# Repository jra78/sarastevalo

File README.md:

# sarastevalo
"Sarastevalo eagle" hekemistosta löytyy piirilevyä varten eagle tiedostot (useampia versioita)
"Sarastevalo arduino" hakemistosta löytyy koodi

in "Sarastevalo eagle"-folder is eagle files (multiple versions)
in "Sarastevalo arduino" folder is code

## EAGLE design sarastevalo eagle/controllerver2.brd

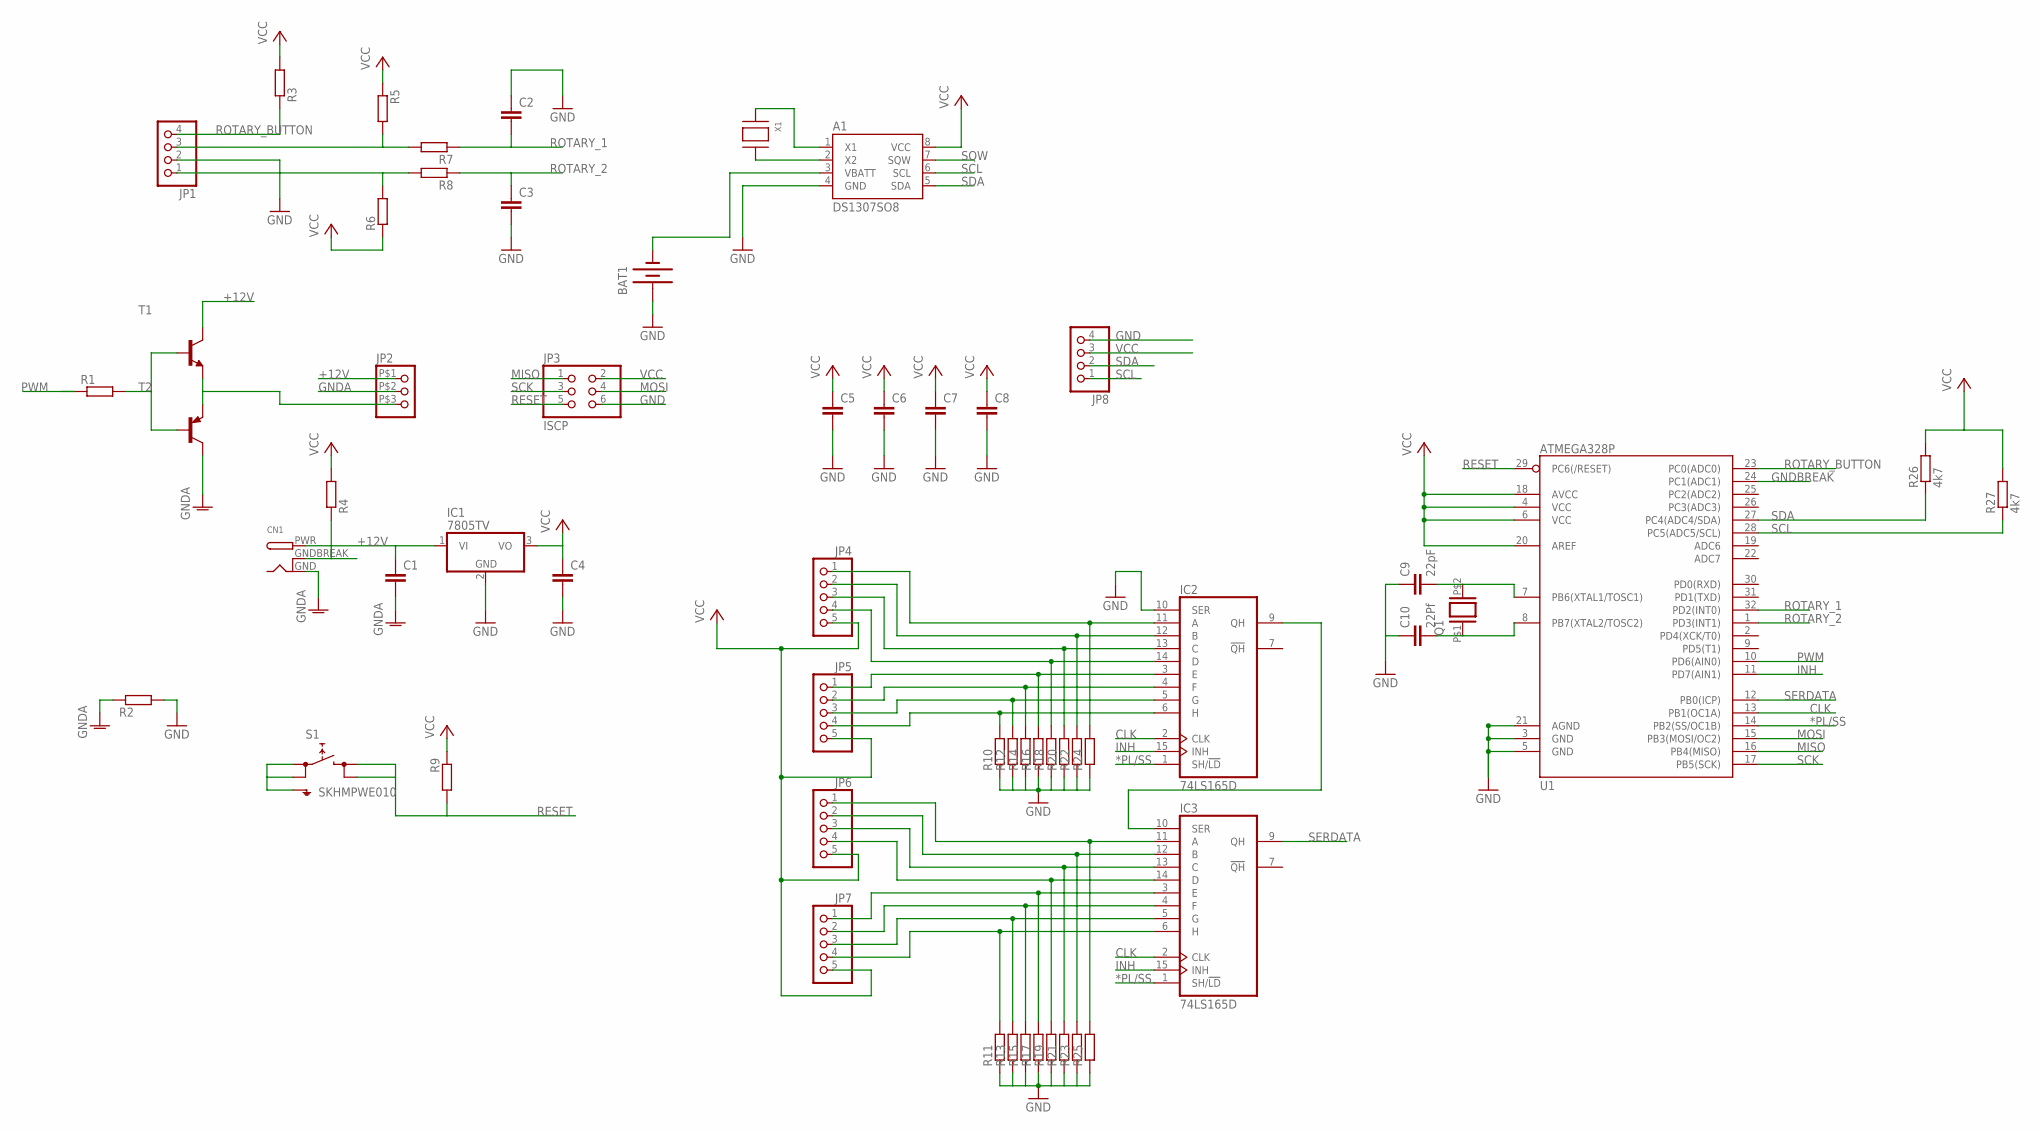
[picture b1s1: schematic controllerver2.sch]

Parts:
A1: DS1307SO8; SO08
BAT1: BATTERY20SMD; BATTCON_20MM
C1, C2, C3, C4, C5, C6, C7, C8: C-EUC0805; C0805
C9: 22pF; C0805
C10: 22Pf; C0805
CN1: DCBARRELPTH; DCJACK_2MM_PTH
IC1: 7805TV; TO220V
IC2, IC3: 74LS165D; SO16
JP1, JP8: PINHD-1X4; 1X04
JP2: PINHD-1X35.08; 1X03/5.08
JP3: ISCP; 2X03
JP4, JP5, JP6, JP7: PINHD-1X5; 1X05
Q1: XTAL; CSM-3X
R1, R2, R3, R4, R5, R6, R7, R8, R9, R10, R11, R12, R13, R14, R15, R16, R17, R18, R19, R20, R21, R22, R23, R24, R25: R-EU_R0805; R0805
R26, R27: 4k7; R0805
S1: SKHMPWE010; SKHMPXE010
T1: BC847-NPN-SOT23-BEC; SOT23-BEC
T2: BC807-16-PNP-SOT23-BEC; SOT23-BEC
U1: ATMEGA328P; TQFP32-08
X1: XTAL-3.2X1.5; XTAL3215

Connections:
*PL/SS: IC2.1 (SH/!LD), IC3.1 (SH/!LD), U1.14 (PB2(SS/OC1B))
+12V: C1.1, CN1.PWR, IC1.1 (VI), JP2.P$1 (1), T1.C
CLK: IC2.2 (CLK), IC3.2 (CLK), U1.13 (PB1(OC1A))
GND: A1.4 (GND), BAT1.1 (+), C2.1, C3.2, C4.2, C5.2, C6.2, C7.2, C8.2, C9.1, C10.1, IC1.2 (GND), IC2.8 (GND), IC2.10 (SER), IC3.8 (GND), JP1.2, JP3.6, JP8.4, R2.2, R10.1, R11.1, R12.1, R13.1, R14.1, R15.1, R16.1, R17.1, R18.1, R19.1, R20.1, R21.1, R22.1, R23.1, R24.1, R25.1, S1.1 (1.1), S1.2 (1.2), S1.5 (SH), U1.3 (GND), U1.5 (GND), U1.21 (AGND)
GNDA: C1.2, CN1.GND, JP2.P$2 (2), R2.1, T2.C
GNDBREAK: CN1.GNDBREAK, R4.1, U1.24 (PC1(ADC1))
INH: IC2.15 (INH), IC3.15 (INH), U1.11 (PD7(AIN1))
MISO: JP3.1, U1.16 (PB4(MISO))
MOSI: JP3.4, U1.15 (PB3(MOSI/OC2))
unnamed: IC2.11 (A), JP4.1, R24.2
unnamed: IC2.12 (B), JP4.2, R22.2
unnamed: IC2.13 (C), JP4.3, R20.2
unnamed: IC2.14 (D), JP4.4, R18.2
unnamed: IC2.3 (E), JP5.1, R16.2
unnamed: IC2.4 (F), JP5.2, R14.2
unnamed: IC2.5 (G), JP5.3, R12.2
unnamed: IC2.6 (H), JP5.4, R10.2
unnamed: IC3.11 (A), JP6.1, R25.2
unnamed: IC3.12 (B), JP6.2, R23.2
unnamed: IC3.13 (C), JP6.3, R21.2
unnamed: IC3.14 (D), JP6.4, R19.2
unnamed: IC3.3 (E), JP7.1, R17.2
unnamed: IC3.4 (F), JP7.2, R15.2
unnamed: IC3.5 (G), JP7.3, R13.2
unnamed: IC3.6 (H), JP7.4, R11.2
unnamed: JP1.3, R5.2, R7.2
unnamed: JP2.P$3 (3), T1.E, T2.E
unnamed: JP1.1, R6.2, R8.2
unnamed: IC2.9 (QH), IC3.10 (SER)
unnamed: A1.3 (VBATT), BAT1.2 (-)
unnamed: C9.2, Q1.P$2 (2), U1.7 (PB6(XTAL1/TOSC1))
unnamed: C10.2, Q1.P$1 (1), U1.8 (PB7(XTAL2/TOSC2))
unnamed: R1.2, T1.B, T2.B
unnamed: A1.2 (X2), X1.P$2
unnamed: A1.1 (X1), X1.P$1
PWM: R1.1, U1.10 (PD6(AIN0))
RESET: JP3.5, R9.2, S1.3 (2.1), S1.4 (2.2), U1.29 (PC6(/RESET))
ROTARY_1: C2.2, R7.1, U1.32 (PD2(INT0))
ROTARY_2: C3.1, R8.1, U1.1 (PD3(INT1))
ROTARY_BUTTON: JP1.4, R3.1, U1.23 (PC0(ADC0))
SCK: JP3.3, U1.17 (PB5(SCK))
SCL: A1.6 (SCL), JP8.1, R27.1, U1.28 (PC5(ADC5/SCL))
SDA: A1.5 (SDA), JP8.2, R26.1, U1.27 (PC4(ADC4/SDA))
SERDATA: IC3.9 (QH), U1.12 (PB0(ICP))
SQW: A1.7 (SQW)
VCC: A1.8 (VCC), C4.1, C5.1, C6.1, C7.1, C8.1, IC1.3 (VO), IC2.16 (VCC), IC3.16 (VCC), JP3.2, JP4.5, JP5.5, JP6.5, JP7.5, JP8.3, R3.2, R4.2, R5.1, R6.1, R9.1, R26.2, R27.2, U1.4 (VCC), U1.6 (VCC), U1.18 (AVCC), U1.20 (AREF)

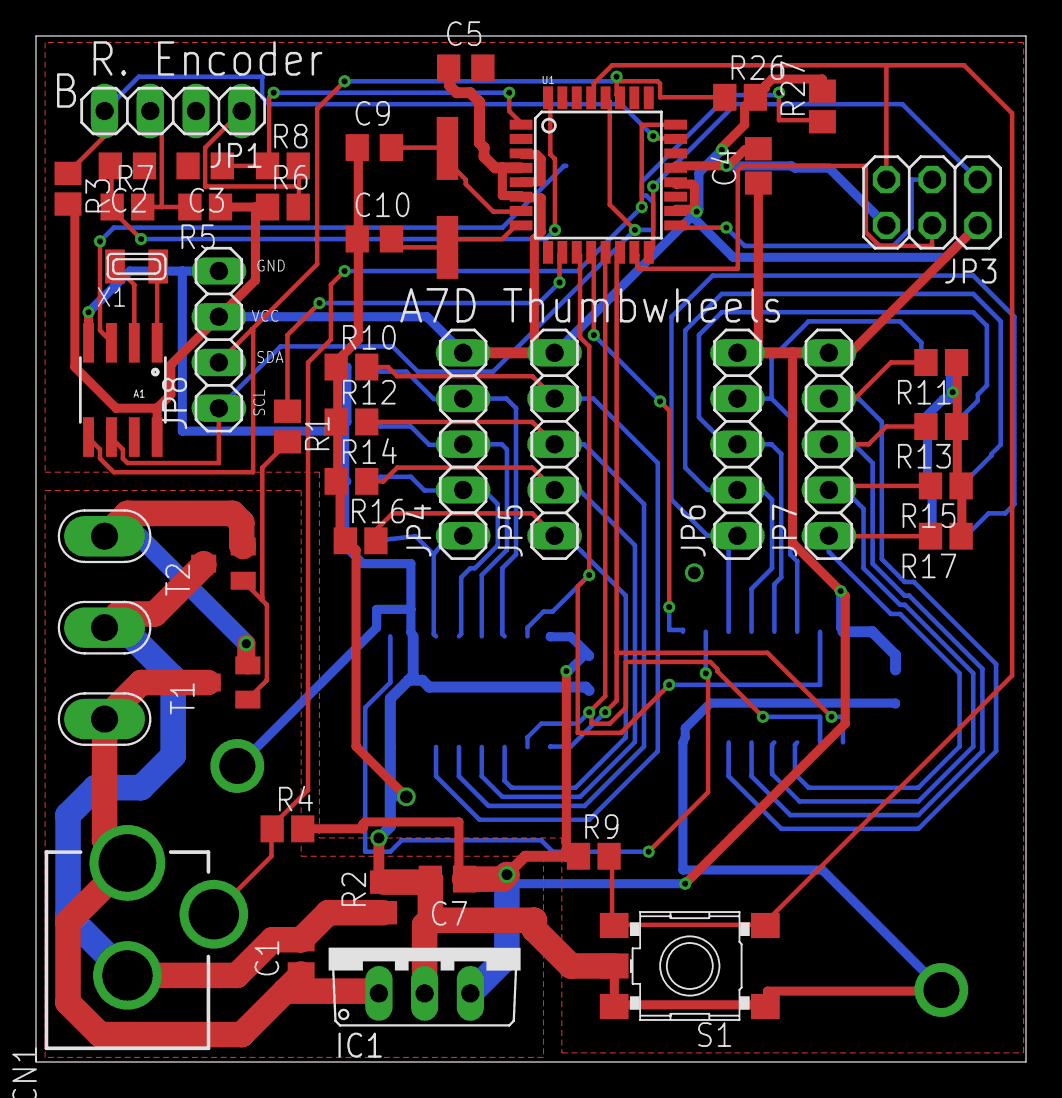
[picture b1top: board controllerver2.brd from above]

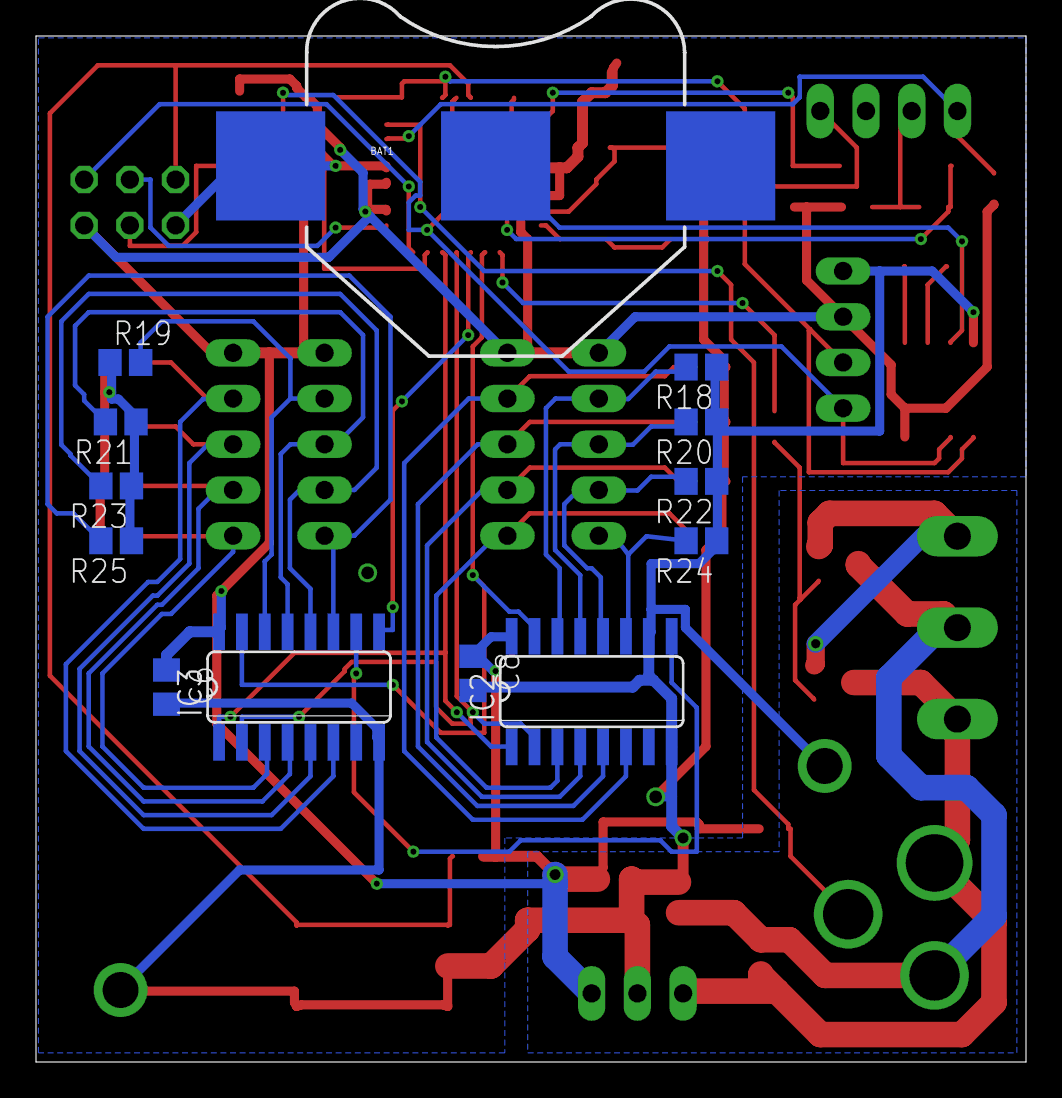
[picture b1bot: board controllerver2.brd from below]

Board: 2 copper layers, 55.0 x 57.0 mm, 57 parts (13 on the bottom side), 45 nets.

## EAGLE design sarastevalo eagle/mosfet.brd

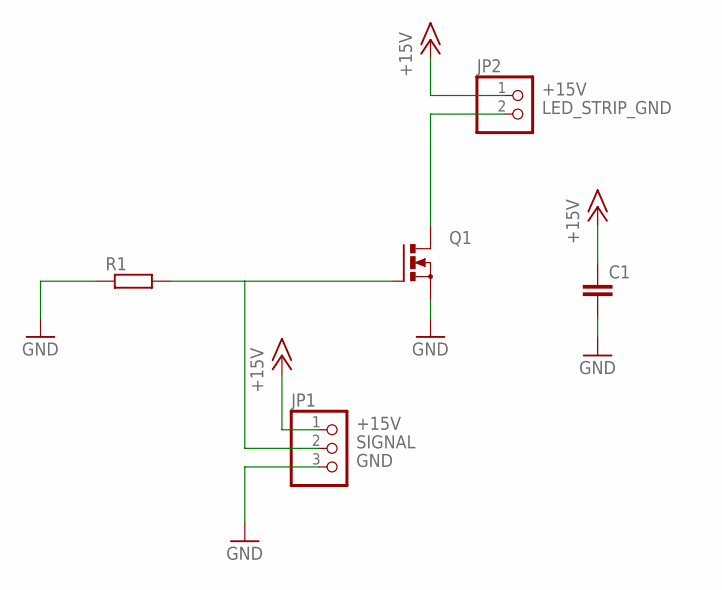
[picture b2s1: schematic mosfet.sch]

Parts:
C1: C-EU050-025X075; C050-025X075
JP1: PINHD-1X3; 1X03
JP2: PINHD-1X2; 1X02
Q1: PMOSFET_NTO220BV; TO220BV
R1: R-EU_M0805; M0805

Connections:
+15V: C1.1, JP1.1, JP2.1
GND: C1.2, JP1.3, Q1.S, R1.1
LED_STRIP_GND: JP2.2, Q1.D
SIGNAL: JP1.2, Q1.G, R1.2

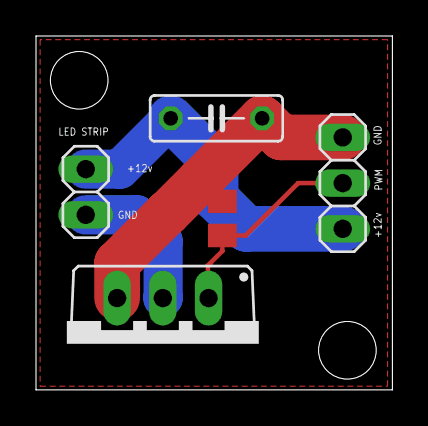
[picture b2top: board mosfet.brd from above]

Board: 2 copper layers, 19.8 x 19.7 mm, 5 parts (0 on the bottom side), 4 nets.

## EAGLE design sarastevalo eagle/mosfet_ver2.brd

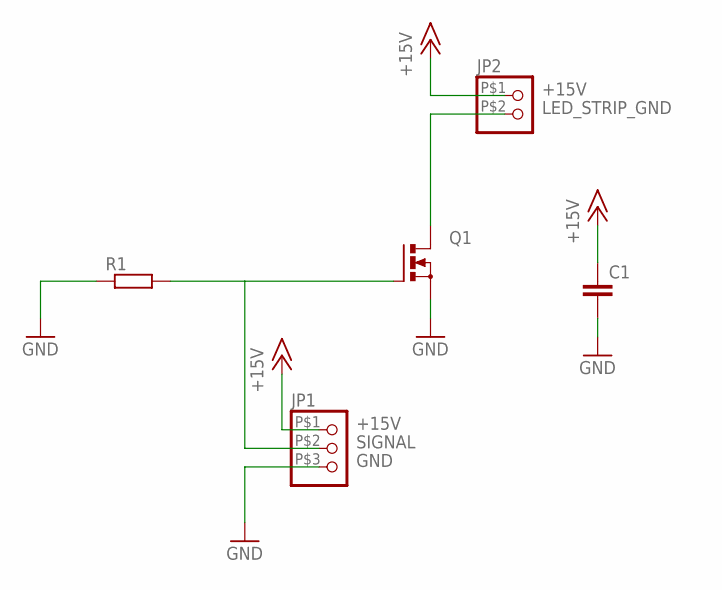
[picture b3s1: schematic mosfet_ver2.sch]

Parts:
C1: C-EU050-025X075; C050-025X075
JP1: PINHD-1X35.08; 1X03/5.08
JP2: PINHD-1X2/5.08; 1X02/5.08
Q1: PMOSFET_NTO220BV; TO220BV
R1: R-EU_M0805; M0805

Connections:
+15V: C1.1, JP1.P$1 (1), JP2.P$1 (1)
GND: C1.2, JP1.P$3 (3), Q1.S, R1.1
LED_STRIP_GND: JP2.P$2 (2), Q1.D
SIGNAL: JP1.P$2 (2), Q1.G, R1.2

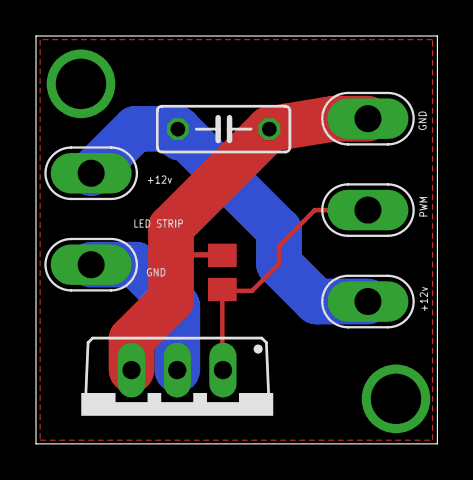
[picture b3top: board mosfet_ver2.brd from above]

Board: 2 copper layers, 22.3 x 22.7 mm, 5 parts (0 on the bottom side), 4 nets.

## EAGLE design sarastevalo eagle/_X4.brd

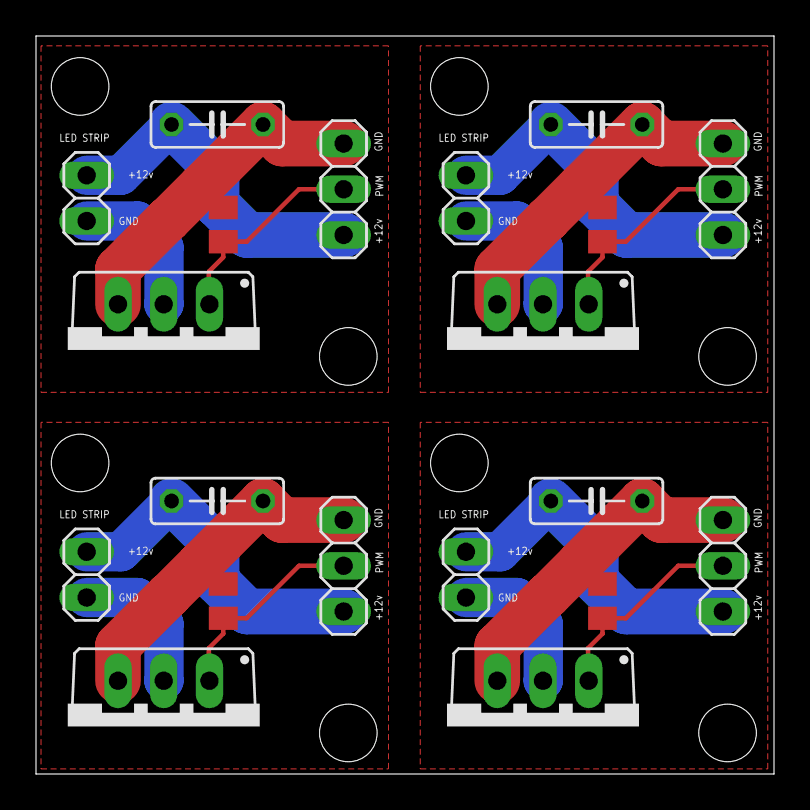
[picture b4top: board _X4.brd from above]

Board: 2 copper layers, 41.0 x 41.0 mm, 20 parts (0 on the bottom side), 16 nets.

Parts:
C1, C2, C3, C4: C050-025X075
JP1, JP3, JP5, JP7: 1X03
JP2, JP4, JP6, JP8: 1X02
Q1, Q2, Q3, Q4: TO220BV
R1, R2, R3, R4: M0805

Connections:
+15V: C1.1, JP1.1, JP2.1
+15V1: C2.1, JP3.1, JP4.1
+15V2: C3.1, JP5.1, JP6.1
+15V3: C4.1, JP7.1, JP8.1
GND: C1.2, JP1.3, Q1.S, R1.1
GND1: C2.2, JP3.3, Q2.S, R2.1
GND2: C3.2, JP5.3, Q3.S, R3.1
GND3: C4.2, JP7.3, Q4.S, R4.1
LED_STRIP_GND: JP2.2, Q1.D
LED_STRIP_GND1: JP4.2, Q2.D
LED_STRIP_GND2: JP6.2, Q3.D
LED_STRIP_GND3: JP8.2, Q4.D
SIGNAL: JP1.2, Q1.G, R1.2
SIGNAL1: JP3.2, Q2.G, R2.2
SIGNAL2: JP5.2, Q3.G, R3.2
SIGNAL3: JP7.2, Q4.G, R4.2

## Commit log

2015-01-12 lisätty tiedostoja
2015-01-12 Changes to be committed: modified: README.md
2015-01-12 Changes to be committed: modified: README.md new file: README.md~
2015-01-12 Changes to be committed: new file: sarastevalo arduino/sarastevalo.ino
2015-01-13 Encoder changes,pwm does not change from 0 to 255 or 255 to 0 so easy

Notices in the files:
parts and their libraries:
SparkFun-DigitalIC: Licensing: Creative Commons ShareAlike 4.0 International - https://creativecommons.org/licenses/by-sa/4.0
